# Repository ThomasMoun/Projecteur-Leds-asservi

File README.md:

# Projecteur-Leds-asservi  

<p align="center"> 

|Etudiants en charge du projet |       
|:----------------------------:|       
|Tom Charbonneau               |       
|Baptiste Gilles               |       
|Ludovic Sercy                 |
|Thomas Mouneyrat              |
|Bassem Barakat                |
|Quentin de La Chaise          |

|Professeurs encadrants le projet |
|:-------------------------------:|
|Nicolas Papazoglou               |
|Laurent Fiack                    |

*N.B. : Ce README s'adresse aux futurs ensearques qui auront le courage de s'aventurer sur le sinueux chemin de ce projet ; il s'adresse aussi aux électroniciens curieux et avide de découvertes ; enfin il s'adresse évidemment à nos chers professeurs.*

## Introduction

Le projecteur Leds est, comme son nom l'indique, un structure permettant l'éclairage coloré et la mise en valeur de décor dans différents évènements plus ou moins festifs.
Un projecteur de ce type doit pouvoir bouger suivant différents axes (2 dans notre cas Tilt-Pan) et le zoom ainsi que la couleur de la lumière émise doivent être ajustables.
Ce projet s'inscrit donc dans les domaines de la lumière et du son, et serait en théorie piloté par un régisseur lors d'évènements.
Ainsi, à la fin de la conception de ce projet on doit pouvoir être capable de le faire bouger en choisissant la direction et l'axe de mouvement, on doit aussi être en mesure de changer la couleur et de centrer la lumière sur des zones précises (tout cela via un unique contrôleur).

## Organisation du dépôt git

Dans ce dépôts git vous trouverez une branche pour chaque grand axe de travail du projet : 
 - Les différentes carte (Led, Alimentation, contrôle etc)
 - La partie mécanique (modélisation 3D)
 - Les parties drivers (moteurs, leds)
 
Dans la branche principale vous trouverez aussi les schémas utilisés dans ce README.

*Logiciels utilisés*

|Conception/Design PCB | Modélisation 3D | Programmation des cartes et définition des connexions |
|:--------------------:|:---------------:|:-----------------------------------------------------:|
|KiCAD 6.0             |Onshape          |STM32CubeIDE et STM32CubeMX                            |

|Alternatives possibles                                                                          |
|:----------------------------------------------------------------------------------------------:|
|Eagle (PCB)     /    Solidworks (onshape a l'avantage d'être gratuit)                           |

|Gestion de projet                                                                               |
|:----------------------------------------------------------------------------------------------:|
|Google Drive/Github/Redmine de l'école                                                          |                   

## Schémas d'architecture Hardware et/ou Software

_<p align = center>Schéma structurel associé à la structure 3D</p>_

*<p align =center>Schéma général d'architecture</p>*

*<p align = center>Schéma commande et puissance</p>*

Ce schéma nous a permis de synthétiser "qui a quel rôle" en commande et en alimentation

## Documentation

*Ce qui marche/Ce qui marche pas*

Général : 

-La carte d'alimentation semble fontionner bien qu'elle n'est pas été testé avec tout, elle possède tous les composants nécessaire à l'alimentation de l'ensemble
- Le réglage en intensité (via le contôleur) de la led issu du pcb "led test" fonctionne, le code qui passe par le DMX est donc correcte.
- Le mouvement du projecteur via le pilotage des moteurs n'est pas fiable, le code et des poids structurels sont à revoir.
- L'architecture du PCB de contrôle est correcte dans l'ensemble et possède tous les composants nécéssaires au bon fonctionnement du projecteur. Le régulateur linéaire est à déplacer car, suite à un soucis d'impression de via, on a rencontré des difficultés à le souder correctement empêchant son fonctionnement. Certaines capacités de découplage sont potentiellement à rapprocher du projecteur.

Point mécanique : 

Certaines des pièces sont à revoir pour la conception, il s'agit d'un prototype et il comporte beaucoup de défaut.

Défaut:
- Axe difficile à monter sur la pièce en U, il faut tordre la pièce en U pour insérer l'axe.
- Pas de buté axial sur l'axe
- tolérance des trous pas assez grands
- Solidité des axes des engrenages faibles
- Cage des engrenages trop rigide
- Montage des vis de la tête de projecteur impossible à cause de la structure en U qui empêche son accès
- Les vis de maintien entre la base et la partie tournante du projecteur étaient difficilement accessibles
    
## TODO
 
- Il reste une grosse partie programmation notamment pour le processeur de la carte de contrôle (centralisation des codes) et le pilotage des moteurs
- La carte Leds complète a été designé, il faut l'imprimer une première fois et la tester
- Reste à traiter le ventilateur ou un système de refroidissement de la struture (ventilo prévue dans la carte d'alimentation)
- Dans la lignée du ventilo, à voir pour un changement de matériau pour la structure ; l'ensemble est amené à chauffer
- Le zoom est une partie qu'on a très peu traité faute de temps, le projet de base est d'utiliser des lentilles placées devant chaque leds et qu'on viendrait éloignées ou rapprochées des leds pour zoomer. Le mouvement se ferait au travers d'un axe interne au projecteur (prévu dans la structure

Point mécanique :
 
Amélioration :
-Tolérance plus grande
-Utiliser un filetage dans les trous au lieu de vis + écrou
-Certains axes pas assez dimensionner pour résister aux contraintes
-Faire une structure moins rigide pour la cage des engrenages

## Deux points techniques importants    
        
### Le DMX

Afin de pouvoir contrôler le projecteur, nous utilisons une table DMX. Celle-ci est composée de différents curseurs, chacun pouvant contrôler un paramètre différent du projecteur. Les paramètres sont les suivants :
- le TILT
- le PAN
- le Zoom
- la couleur

Certains paramètres nécessitent plusieurs curseurs. En effet, un curseur permet de sélectionner une valeur entre 0 et 255. Pour les moteurs, par exemple, comme nous désirons pouvoir faire une rotation du projecteur de 540 degrés de tilt et 270 degrés de pan, et que les moteurs pas a pas choisi (NEMA 17) ont une résolution de 1,8 degré par pas et que nous désirons implémenter le microstepping pour plus de précision, il est nécessaire d’utiliser plusieurs curseurs. De la même manière, pour contrôler les LEDs, il faut choisir avec des curseurs indépendants les valeurs de Rouge, Vert, Bleu et Blanc.

La table DMX utilise le protocole DMX 512, cela permet d’utiliser un seul câble avec paire différentiel pour contrôler un grand nombre de paramètres et d’appareils. La trame DMX se présente de cette manière :

*<p align =center>Trame DMX</p>*

Chaque trame commence par un Break puis un MAB. Il y a ensuite 513 canaux DMX, le premier est le start code qui est utilisé pour paramétrer certains appareils mais inutile dans notre cas. Les 512 canaux suivants contiennent les valeurs prises par les différents curseurs.

Le signal étant transmis sur une paire différentielle, il est nécessaire pour le décoder de le passer sur un seul fil. Pour cela, on utilise un transmitter RS-485. 
Afin de décoder la trame DMX, on utilise de l’UART. Il est nécessaire de détecter le début de la trame pour pouvoir connaitre les valeurs correspondantes aux bons curseurs. Pour cela on utilise une Frame Error de l’UART.

Une fois ces valeurs récupérées, on peut les transmettre aux drivers moteurs et LEDs pour effectuer les actions demandées.

### Driver Moteur

#### Le fonctionnement

L’objectif était de réaliser des drivers pour des moteurs pas a pas capable de faire du microstepping. Chaque driver est composé d’un STM32G0 en communication avec le PCB de contrôle qui lui fourni la position à atteindre. Le STM32 pilote ensuite des ponts en H associés aux deux phases du moteur.

Les moteurs choisis sont des NEMA 14 et NEMA 17, chacun de ces moteurs possède des caractéristiques différentes mais comme ils seront asservi en courant, on peut conserver le même driver et le programmer différemment pour éviter que ceux-ci ne grillent. Ces moteurs sont composés de deux phases A et B, ce sont les enroulements des moteurs. Ces enroulements permettent de créer un champ magnétique permettant d’orienter le stator dans la direction voulu.

<p align =center><i>Phases du moteur</i></p>

Pour alimenter les enroulements, on utilise deux ponts en H ce qui nous permet de choisir le sens d’alimentation de chacune des phases.

<p align =center><i>Les deux états du pont en H</i></p>

En full step, ces phases sont alimentées alternativement dans un sens puis dans l’autre de manière à orienter le stator dans l’axe des enroulements.

<p align =center><i>Ordre d'alimentation des phases</i></p>

Pour le microstepping, on alimente simultanément les deux phases à différentes intensités afin d’aligner le rotor entre deux phases, cela nous permet d’augmenter le nombre de pas. On utilise le wave microstepping pour garder un couple constant au cours du temps.

<p align =center><i>Ordre d'alimentation des phases pour le Half-Step</i></p>

Pour un plus grand nombre de pas, on obtient les formes de courant suivantes :

On peut donc relier le courant au numéro du pas désiré par les équations suivantes :
- Ia = sin(num_pas * 360/32) * Imax
- Ib = cos(num_pas * 360/32) * Imax

Afin de d’asservir le courant arrivant dans chaque phase, on utilise un hacheur et un détecteur de courant pour chaque phase.

### Améliorations

- Le PCB n’ayant pas fonctionné, il est nécéssaire d’effectuer de nouveaux tests.
- Afin de pouvoir asservir le courant, il faut soit rajouter un hacheur soit dissocier les deux cotés de chaque pont en H pour pouvoir l'utiliser en hacheur (cette methode nécéssite des sorties PWM supplémentaires sur le STM32).
- Choisir mieux les composants pour qu'ils aient des tensions d'alimentation similaires afin de réduire le nombre de tensions d'alimentations différentes sur le driver.

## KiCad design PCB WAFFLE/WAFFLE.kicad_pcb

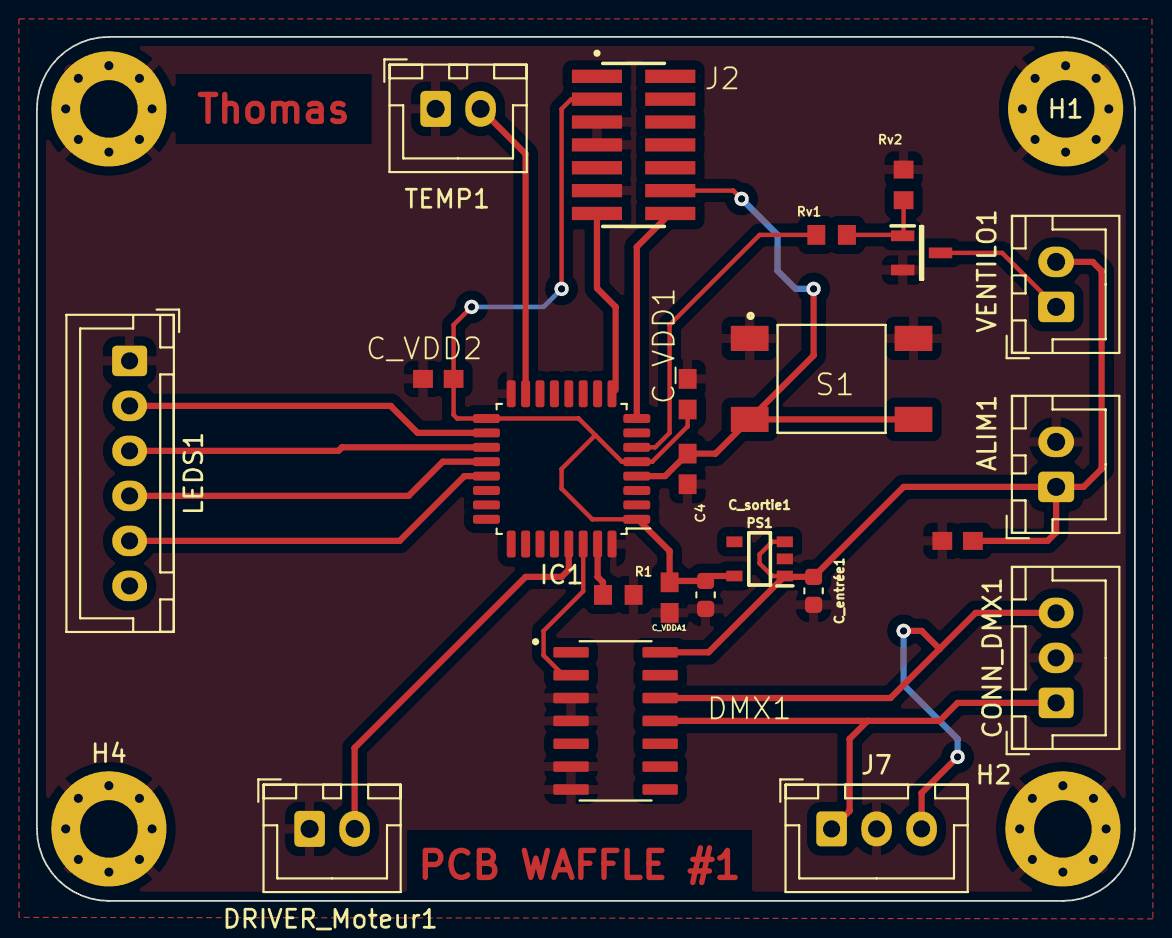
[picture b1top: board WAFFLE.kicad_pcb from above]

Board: 2 copper layers, 61.0 x 48.0 mm, 27 parts (0 on the bottom side), 19 nets.

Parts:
ALIM1: Conn_01x02; JST_XH_B2B-XH-A_1x02_P2.50mm_Vertical
C4: 0.1uF; C0603
CONN_DMX1: Conn_01x03_Male; JST_XH_B3B-XH-A_1x03_P2.50mm_Vertical
C_Decoupl_Connecteur1: 100uF; C0603
C_VDD1, C_VDD2: 100nF; C0603
C_VDDA1: 100nF; C0603
C_entrée1: 1uF; C_0603_1608Metric
C_sortie1: 4.7uF; C_0603_1608Metric
DMX1: SOIC127P600X175-14N
DRIVER_Moteur1: Conn_01x02; JST_XH_B2B-XH-A_1x02_P2.50mm_Vertical
H1, H2, H3, H4: MountingHole_Pad; MountingHole_3.2mm_M3_Pad_Via
IC1: STM32L412KBT6; LQFP-32_7x7mm_P0.8mm
J2: FTSH-107-01-L-DV; SAMTEC_FTSH-107-01-L-DV
J7: Conn_01x03_Male; JST_XH_B3B-XH-A_1x03_P2.50mm_Vertical
LEDS1: PINHD-1X6; JST_XH_B6B-XH-A_1x06_P2.50mm_Vertical
PS1: BU33SD5WG-TR; RegLIN
Q1: SQ2310ES-T1_GE3; SOT95P237X112-3N
R1: 100k; R0603
Rv1: 22; R0603
Rv2: 10k; R0603
S1: 2-1437565-7; SW_2-1437565-7
TEMP1: Conn_01x02; JST_XH_B2B-XH-A_1x02_P2.50mm_Vertical
VENTILO1: Conn_01x02; JST_XH_B2B-XH-A_1x02_P2.50mm_Vertical

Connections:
+3.3V: C_VDD1.1, C_VDD2.1, C_VDDA1.1, C_sortie1.1, IC1.1 (VDD_1), IC1.5 (VDDA/VREF+), IC1.17 (VDD_2), J2.03, PS1.5 (VOUT)
+5V: ALIM1.1, C_Decoupl_Connecteur1.2, C_entrée1.1, DMX1.14 (VCC), PS1.1 (VIN), PS1.3 (STBY), VENTILO1.2
ADC_Température_ventilo: IC1.15 (PB1), TEMP1.2
GND: ALIM1.2, C4.2, CONN_DMX1.2, C_Decoupl_Connecteur1.1, C_VDD1.2, C_VDD2.2, C_VDDA1.2, C_entrée1.2, C_sortie1.2, DMX1.3 (RE/), DMX1.4 (DE), DMX1.6 (GND_1), DMX1.7 (GND_2), DRIVER_Moteur1.1, H1.1, H2.1, H3.1, H4.1, IC1.16 (VSS_1), IC1.32 (VSS_2), J2.05, J2.07, J2.11, J7.2, LEDS1.1, PS1.2 (GND), Q1.2, R1.2, Rv2.1, S1.1, S1.2, TEMP1.1
NRST: C4.1, IC1.4 (NRST), J2.12, S1.3, S1.4
unnamed: CONN_DMX1.1, DMX1.11 (B), J7.1
unnamed: CONN_DMX1.3, DMX1.12 (A), J7.3
unnamed: IC1.31 (PH3-BOOT0), R1.1
unnamed: Q1.1, Rv1.2, Rv2.2
unnamed: Q1.3, VENTILO1.1
PWM_Leds_B: IC1.19 (PA9), LEDS1.3
PWM_Leds_G: IC1.20 (PA10), LEDS1.4
PWM_Leds_R: IC1.21 (PA11), LEDS1.5
PWM_Leds_W: IC1.18 (PA8), LEDS1.2
PWM_Ventilateur: IC1.6 (PA0-CK_IN), Rv1.1
UART_Driver_moteur: DRIVER_Moteur1.2, IC1.29 (PB6)
UART_RS485_DMX: DMX1.2 (RO), IC1.30 (PB7)
VCP_UART_RX: IC1.9 (PA3), J2.13
VCP_UART_TX: IC1.8 (PA2), J2.14

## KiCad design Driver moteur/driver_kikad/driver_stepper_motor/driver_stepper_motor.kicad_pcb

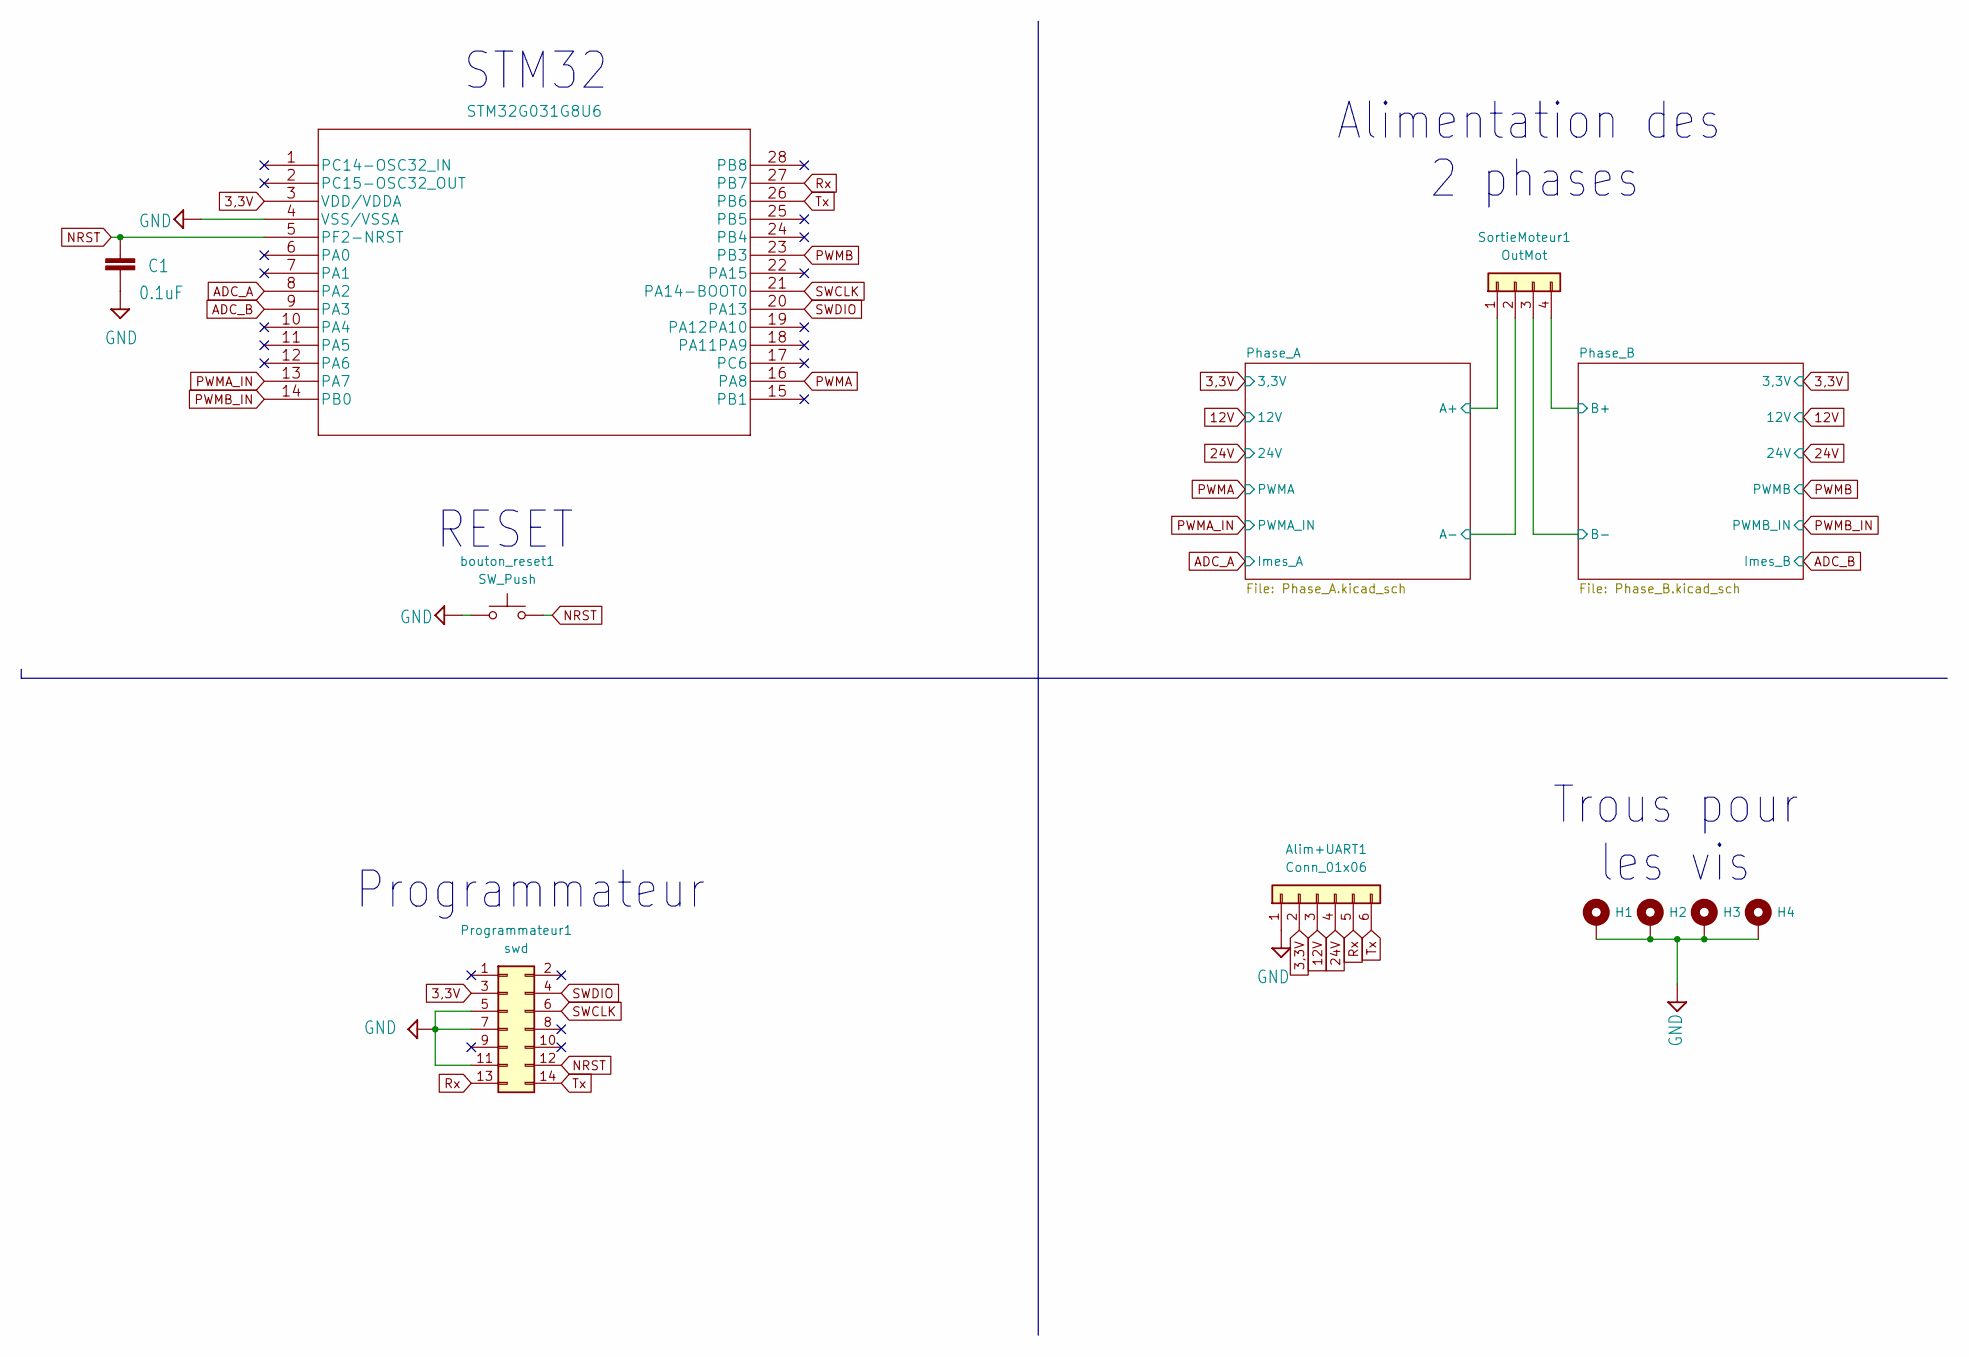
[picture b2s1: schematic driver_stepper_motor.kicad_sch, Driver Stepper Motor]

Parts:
Alim+UART1: Conn_01x06; JST_XH_B6B-XH-A_1x06_P2.50mm_Vertical
C1: 0.1uF; C_0603_1608Metric
H1, H2, H3, H4: MountingHole_Pad; MountingHole_3.2mm_M3_Pad_Via
Programmateur1: swd; PinHeader_2x07_P1.27mm_Vertical_SMD
SortieMoteur1: OutMot; JST_XH_B4B-XH-A_1x04_P2.50mm_Vertical
U1: STM32G031G8U6; QFN-28_4x4mm_P0.5mm
bouton_reset1: SW_Push; SW_2-1437565-7

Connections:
3,3V: Alim+UART1.2, Programmateur1.3, U1.3 (VDD/VDDA); also elsewhere on the board
12V: Alim+UART1.3; also elsewhere on the board
24V: Alim+UART1.4; also elsewhere on the board
/Phase_A/A+: SortieMoteur1.1; also elsewhere on the board
/Phase_A/A-: SortieMoteur1.2; also elsewhere on the board
/Phase_B/B+: SortieMoteur1.4; also elsewhere on the board
/Phase_B/B-: SortieMoteur1.3; also elsewhere on the board
ADC_A: U1.8 (PA2); also elsewhere on the board
ADC_B: U1.9 (PA3); also elsewhere on the board
GND: Alim+UART1.1, C1.2, H1.1, H2.1, H3.1, H4.1, Programmateur1.5, Programmateur1.7, Programmateur1.11, U1.4 (VSS/VSSA), bouton_reset1.1; also elsewhere on the board
NRST: C1.1, Programmateur1.12, U1.5 (PF2-NRST), bouton_reset1.2
PWMA: U1.16 (PA8); also elsewhere on the board
PWMA_IN: U1.13 (PA7); also elsewhere on the board
PWMB: U1.23 (PB3); also elsewhere on the board
PWMB_IN: U1.14 (PB0); also elsewhere on the board
Rx: Alim+UART1.5, Programmateur1.13, U1.27 (PB7)
SWCLK: Programmateur1.6, U1.21 (PA14-BOOT0)
SWDIO: Programmateur1.4, U1.20 (PA13)
Tx: Alim+UART1.6, Programmateur1.14, U1.26 (PB6)

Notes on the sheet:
Trous pour les vis
RESET
Programmateur
STM32
Alimentation des 2 phases

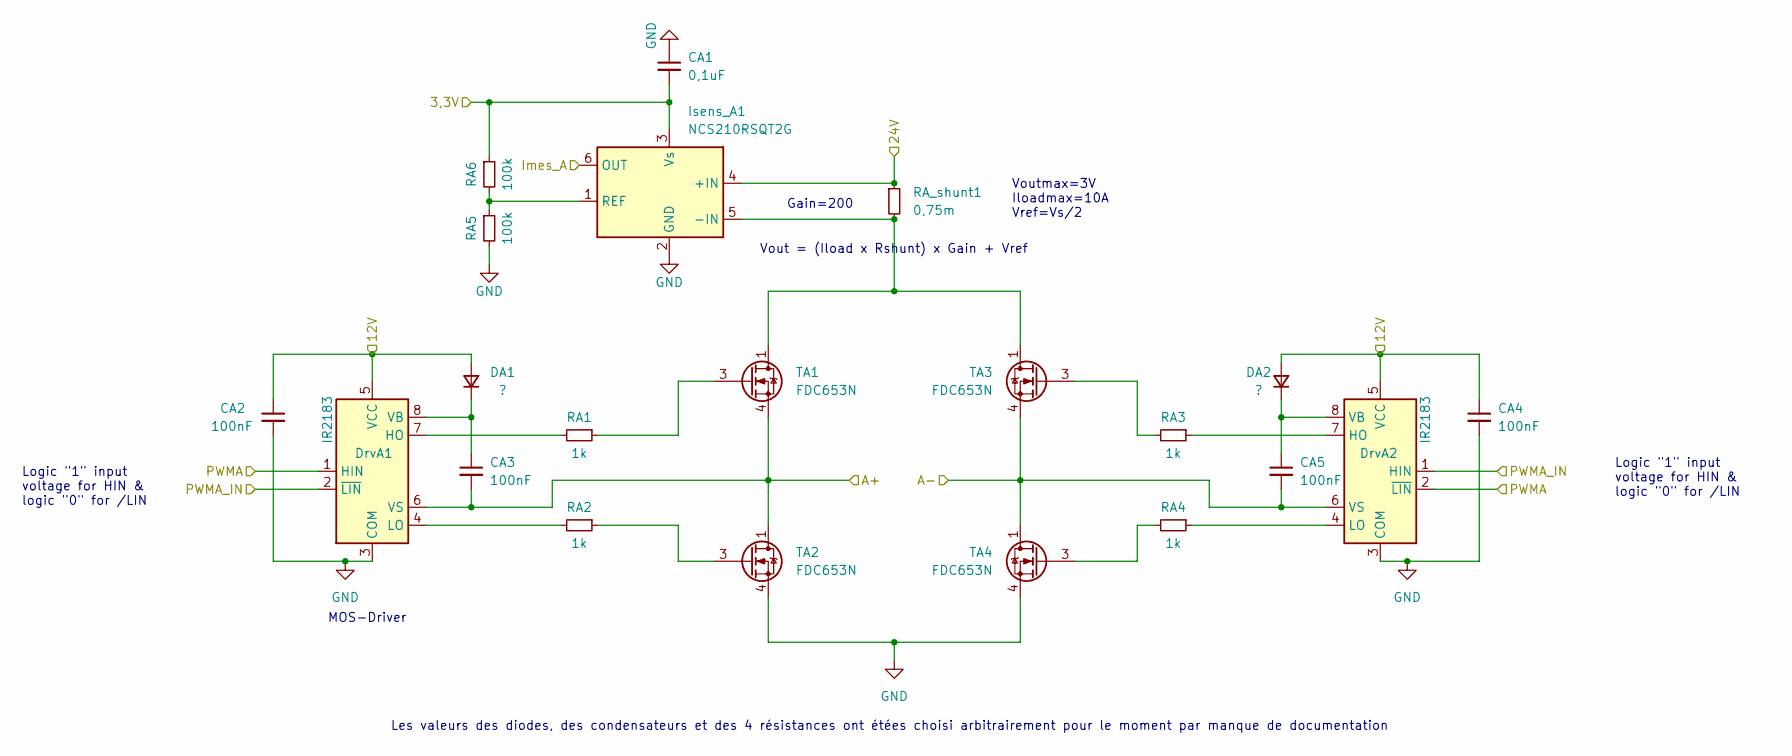
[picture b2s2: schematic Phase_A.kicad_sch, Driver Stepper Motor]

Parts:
CA1: 0,1uF; C_0603_1608Metric
CA2, CA3, CA4, CA5: 100nF; C_0603_1608Metric
DA1, DA2: ?; D_0603_1608Metric
DrvA1, DrvA2: IR2183; SOIC-8_3.9x4.9mm_P1.27mm
Isens_A1: NCS210RSQT2G; SOT-363_SC-70-6
RA1, RA2, RA3, RA4: 1k; R_0603_1608Metric
RA5, RA6: 100k; R_0603_1608Metric
RA_shunt1: 0,75m; R_0603_1608Metric
TA1, TA2, TA3, TA4: FDC653N; SuperSOT-6

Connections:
3,3V: CA1.2, Isens_A1.3 (Vs), RA6.1; also elsewhere on the board
12V: CA2.1, CA4.1, DA1.2 (A), DA2.2 (A), DrvA1.5 (VCC), DrvA2.5 (VCC); also elsewhere on the board
24V: Isens_A1.4 (+IN), RA_shunt1.1; also elsewhere on the board
/Phase_A/A+: CA3.2, DrvA1.6 (VS), TA1.4 (S), TA2.1 (D), TA2.2 (D), TA2.5 (D), TA2.6 (D); also elsewhere on the board
/Phase_A/A-: CA5.2, DrvA2.6 (VS), TA3.4 (S), TA4.1 (D), TA4.2 (D), TA4.5 (D), TA4.6 (D); also elsewhere on the board
ADC_A: Isens_A1.6 (OUT); also elsewhere on the board
GND: CA1.1, CA2.2, CA4.2, DrvA1.3 (COM), DrvA2.3 (COM), Isens_A1.2 (GND), RA5.2, TA2.4 (S), TA4.4 (S); also elsewhere on the board
unnamed: CA3.1, DA1.1 (K), DrvA1.8 (VB)
unnamed: CA5.1, DA2.1 (K), DrvA2.8 (VB)
unnamed: DrvA1.4 (LO), RA2.2
unnamed: DrvA1.7 (HO), RA1.2
unnamed: DrvA2.4 (LO), RA4.1
unnamed: DrvA2.7 (HO), RA3.1
unnamed: Isens_A1.1 (REF), RA5.1, RA6.2
unnamed: Isens_A1.5 (-IN), RA_shunt1.2, TA1.1 (D), TA1.2 (D), TA1.5 (D), TA1.6 (D), TA3.1 (D), TA3.2 (D), TA3.5 (D), TA3.6 (D)
unnamed: RA1.1, TA1.3 (G)
unnamed: RA2.1, TA2.3 (G)
unnamed: RA3.2, TA3.3 (G)
unnamed: RA4.2, TA4.3 (G)
PWMA: DrvA1.1 (HIN), DrvA2.2 (~LIN); also elsewhere on the board
PWMA_IN: DrvA1.2 (~LIN), DrvA2.1 (HIN); also elsewhere on the board

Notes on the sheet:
MOS-Driver
Gain=200
Logic "1" input voltage for HIN & logic "0" for /LIN
Vout = (Iload x Rshunt) x Gain + Vref
Voutmax=3V Iloadmax=10A Vref=Vs/2
Les valeurs des diodes, des condensateurs et des 4 résistances ont étées choisi arbitrairement pour le moment par manque de documentation

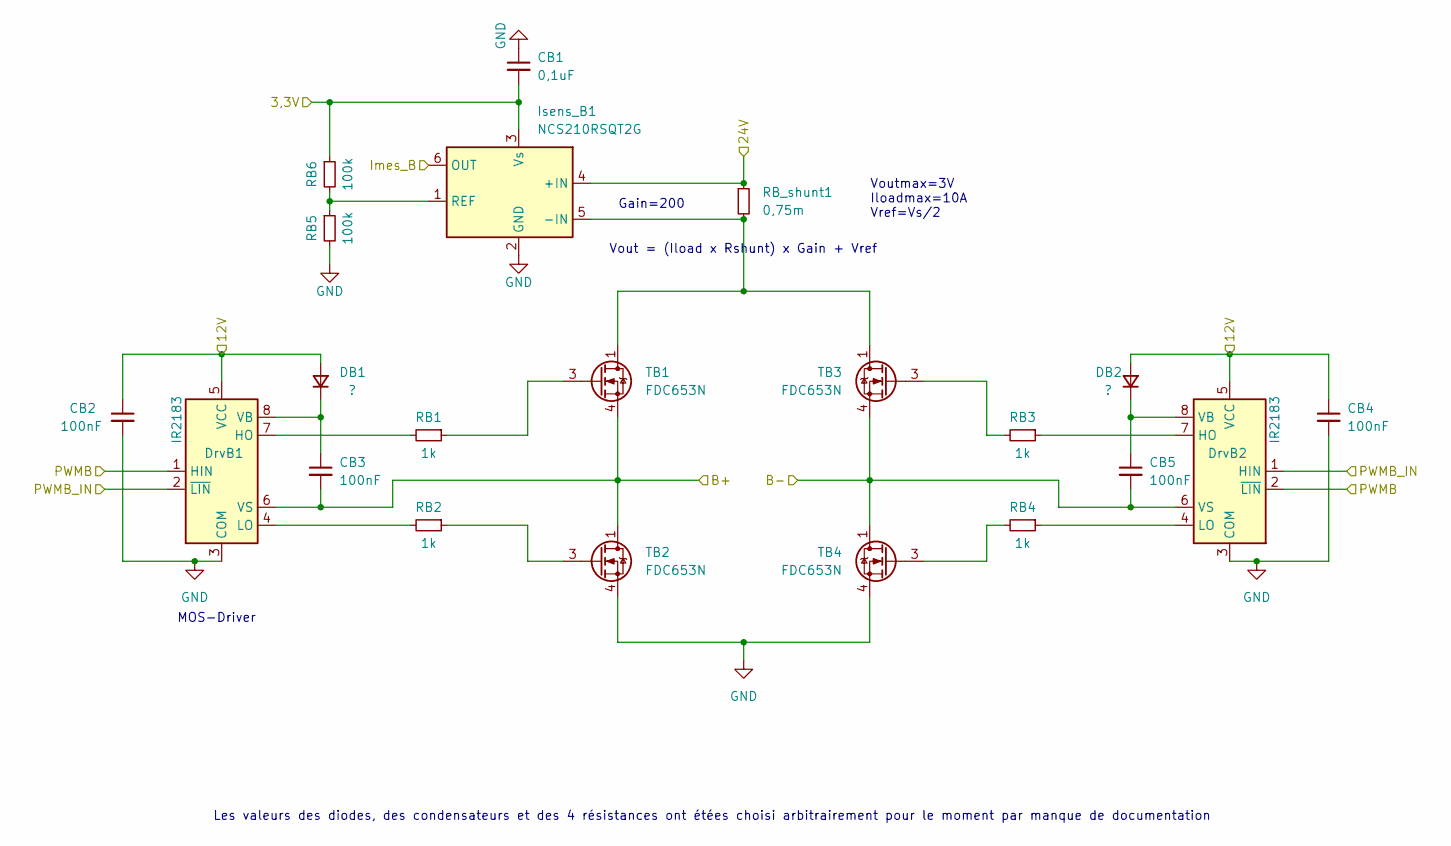
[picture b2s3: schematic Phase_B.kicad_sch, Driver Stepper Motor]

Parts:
CB1: 0,1uF; C_0603_1608Metric
CB2, CB3, CB4, CB5: 100nF; C_0603_1608Metric
DB1, DB2: ?; D_0603_1608Metric
DrvB1, DrvB2: IR2183; SOIC-8_3.9x4.9mm_P1.27mm
Isens_B1: NCS210RSQT2G; SOT-363_SC-70-6
RB1, RB2, RB3, RB4: 1k; R_0603_1608Metric
RB5, RB6: 100k; R_0603_1608Metric
RB_shunt1: 0,75m; R_0603_1608Metric
TB1, TB2, TB3, TB4: FDC653N; SuperSOT-6

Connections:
3,3V: CB1.2, Isens_B1.3 (Vs), RB6.1; also elsewhere on the board
12V: CB2.1, CB4.1, DB1.2 (A), DB2.2 (A), DrvB1.5 (VCC), DrvB2.5 (VCC); also elsewhere on the board
24V: Isens_B1.4 (+IN), RB_shunt1.1; also elsewhere on the board
/Phase_B/B+: CB3.2, DrvB1.6 (VS), TB1.4 (S), TB2.1 (D), TB2.2 (D), TB2.5 (D), TB2.6 (D); also elsewhere on the board
/Phase_B/B-: CB5.2, DrvB2.6 (VS), TB3.4 (S), TB4.1 (D), TB4.2 (D), TB4.5 (D), TB4.6 (D); also elsewhere on the board
ADC_B: Isens_B1.6 (OUT); also elsewhere on the board
GND: CB1.1, CB2.2, CB4.2, DrvB1.3 (COM), DrvB2.3 (COM), Isens_B1.2 (GND), RB5.2, TB2.4 (S), TB4.4 (S); also elsewhere on the board
unnamed: CB3.1, DB1.1 (K), DrvB1.8 (VB)
unnamed: CB5.1, DB2.1 (K), DrvB2.8 (VB)
unnamed: DrvB1.4 (LO), RB2.2
unnamed: DrvB1.7 (HO), RB1.2
unnamed: DrvB2.4 (LO), RB4.1
unnamed: DrvB2.7 (HO), RB3.1
unnamed: Isens_B1.1 (REF), RB5.1, RB6.2
unnamed: Isens_B1.5 (-IN), RB_shunt1.2, TB1.1 (D), TB1.2 (D), TB1.5 (D), TB1.6 (D), TB3.1 (D), TB3.2 (D), TB3.5 (D), TB3.6 (D)
unnamed: RB1.1, TB1.3 (G)
unnamed: RB2.1, TB2.3 (G)
unnamed: RB3.2, TB3.3 (G)
unnamed: RB4.2, TB4.3 (G)
PWMB: DrvB1.1 (HIN), DrvB2.2 (~LIN); also elsewhere on the board
PWMB_IN: DrvB1.2 (~LIN), DrvB2.1 (HIN); also elsewhere on the board

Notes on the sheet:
Gain=200
MOS-Driver
Vout = (Iload x Rshunt) x Gain + Vref
Voutmax=3V Iloadmax=10A Vref=Vs/2
Les valeurs des diodes, des condensateurs et des 4 résistances ont étées choisi arbitrairement pour le moment par manque de documentation

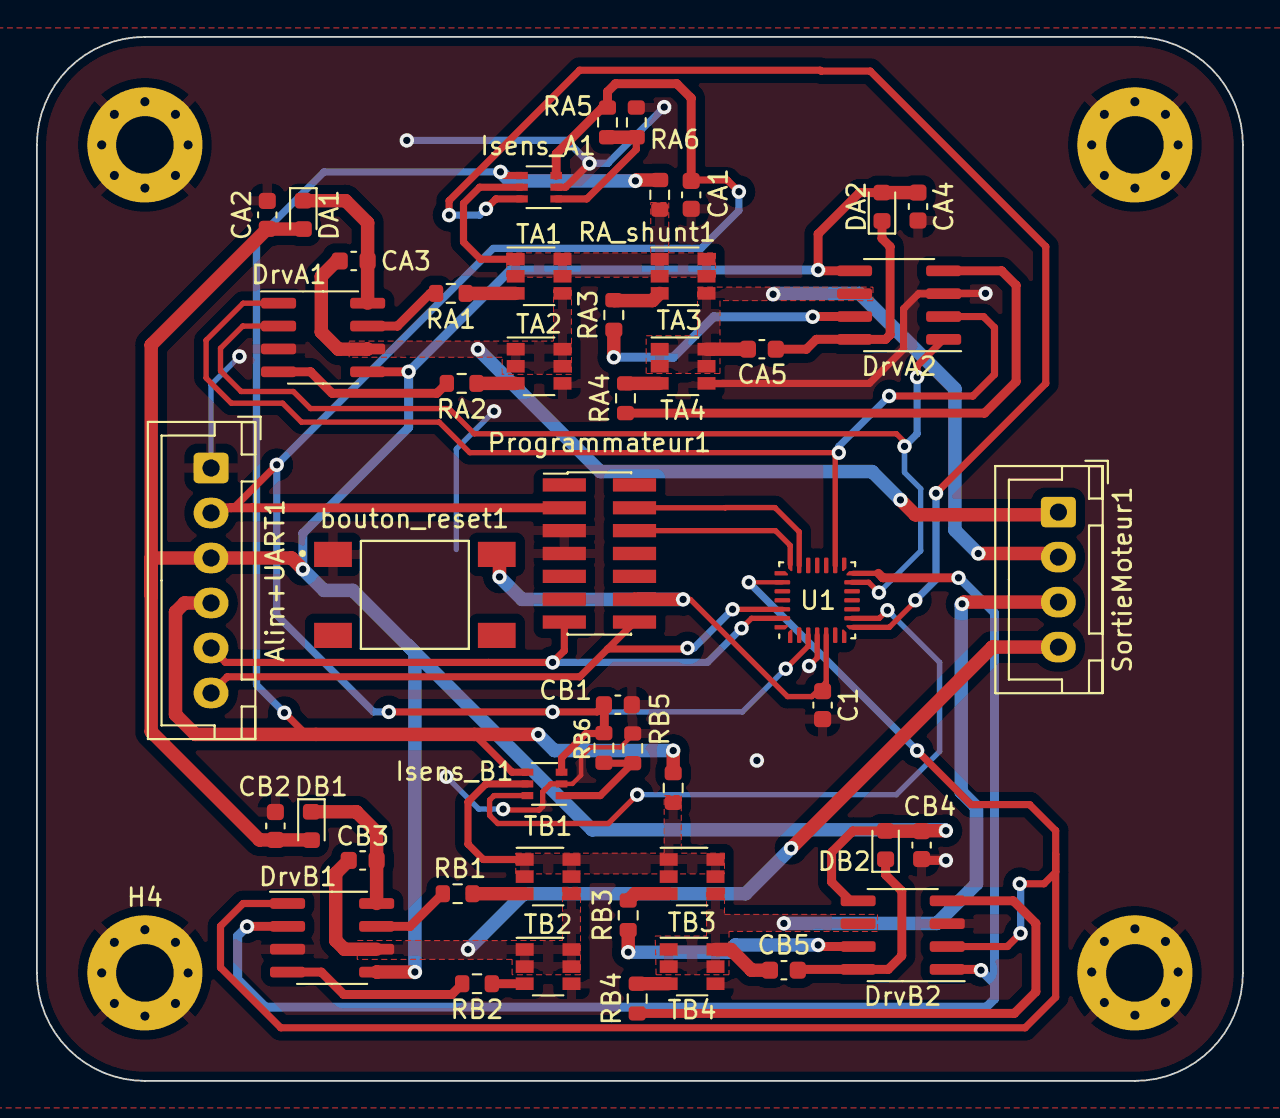
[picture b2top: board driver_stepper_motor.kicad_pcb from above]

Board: 2 copper layers, 67.0 x 58.0 mm, 52 parts (0 on the bottom side), 43 nets.

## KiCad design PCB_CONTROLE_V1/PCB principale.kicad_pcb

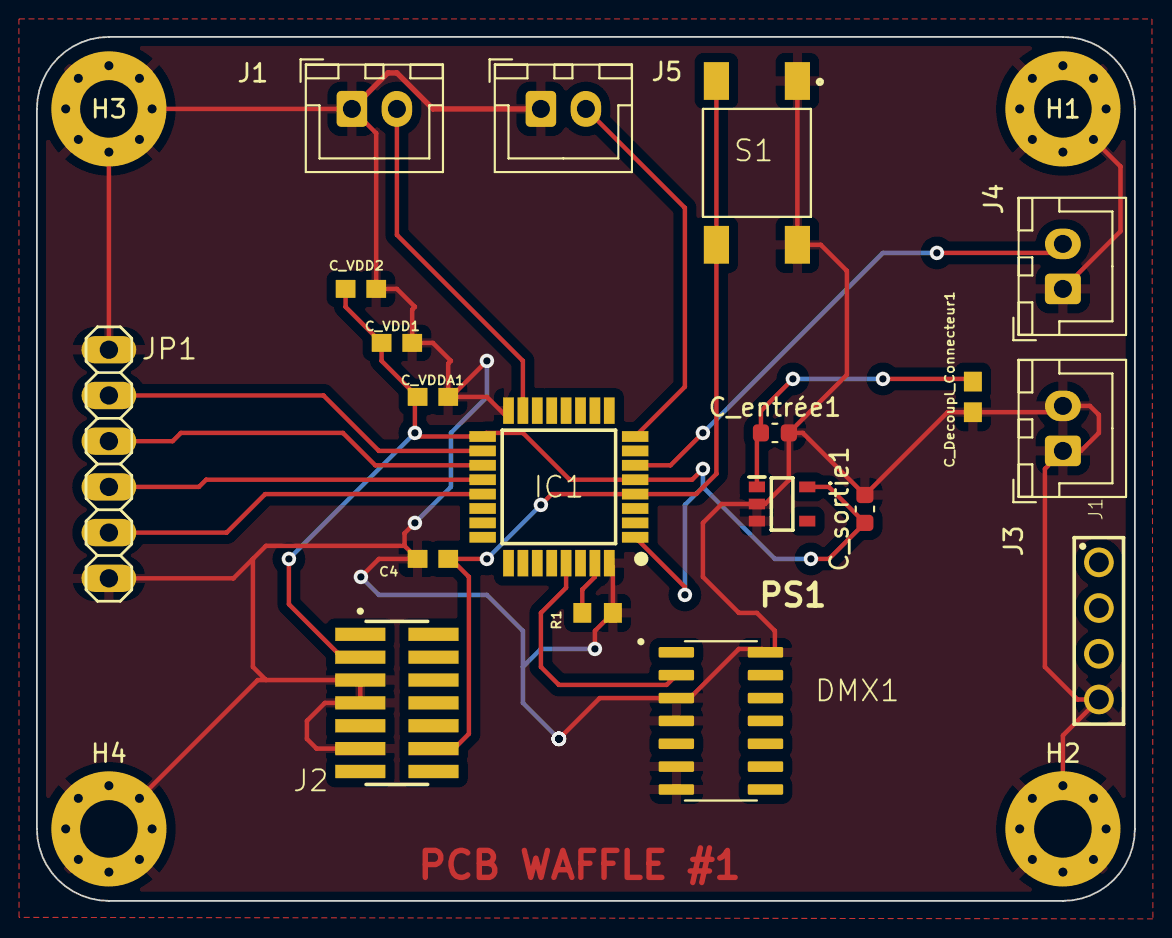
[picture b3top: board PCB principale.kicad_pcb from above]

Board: 2 copper layers, 61.0 x 48.0 mm, 23 parts (0 on the bottom side), 13 nets.

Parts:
C4: 0.1uF; C0603
C_Decoupl_Connecteur1: 100uF; C0603
C_VDD1, C_VDD2: 100nF; C0603
C_VDDA1: 100nF; C0603
C_entrée1: 1uF; C_0603_1608Metric
C_sortie1: 1uF; C_0603_1608Metric
DMX1: SOIC127P600X175-14N
H1, H2, H3, H4: MountingHole_Pad; MountingHole_3.2mm_M3_Pad_Via
IC1: STM32L412KBT6; QFP80P900X900X160-32N
J1, J3, J4, J5: Conn_01x02; JST_XH_B2B-XH-A_1x02_P2.50mm_Vertical
J1#2: 61300411121
J2: FTSH-107-01-L-DV; SAMTEC_FTSH-107-01-L-DV
JP1: PINHD-1X6; 1X06
PS1: BU33SD5WG-TR; SOT95P280X125-5N
R1: 100k; R0603
S1: 2-1437565-7; SW_2-1437565-7

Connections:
5V_RegLin_RSDMX: C4.2, C_Decoupl_Connecteur1.1, C_VDD1.2, C_VDD2.2, C_VDDA1.2, C_entrée1.2, C_sortie1.2, DMX1.3 (RE/), DMX1.4 (DE), DMX1.6 (GND_1), DMX1.7 (GND_2), DMX1.14 (VCC), H1.1, H2.1, H3.1, H4.1, IC1.16 (VSS_1), IC1.32 (VSS_2), J1.1, J1#2.4, J2.05, J2.07, J2.11, J3.1, J3.2, J4.1, J5.1, JP1.1, JP1.6, PS1.2 (GND), PS1.3 (STBY), R1.2, S1.1, S1.2
+3.3V: C_VDD1.1, C_VDD2.1, C_VDDA1.1, C_sortie1.1, IC1.1 (VDD_1), IC1.5 (VDDA/VREF+), IC1.17 (VDD_2), J2.03, PS1.5 (VOUT)
ADC_Température_ventilo: IC1.15 (PB1), J1.2
NRST: C4.1, IC1.4 (NRST), J2.12, S1.3, S1.4
unnamed: C_Decoupl_Connecteur1.2, C_entrée1.1, PS1.1 (VIN)
unnamed: IC1.31 (PH3-BOOT0), R1.1
PWM_Leds_B: IC1.19 (PA9), JP1.3
PWM_Leds_G: IC1.20 (PA10), JP1.4
PWM_Leds_R: IC1.21 (PA11), JP1.5
PWM_Leds_W: IC1.18 (PA8), JP1.2
PWM_Ventilateur: IC1.6 (PA0-CK_IN), J4.2
UART_Driver_moteur: IC1.8 (PA2), J5.2
UART_RS485_DMX: DMX1.2 (RO), IC1.29 (PB6)

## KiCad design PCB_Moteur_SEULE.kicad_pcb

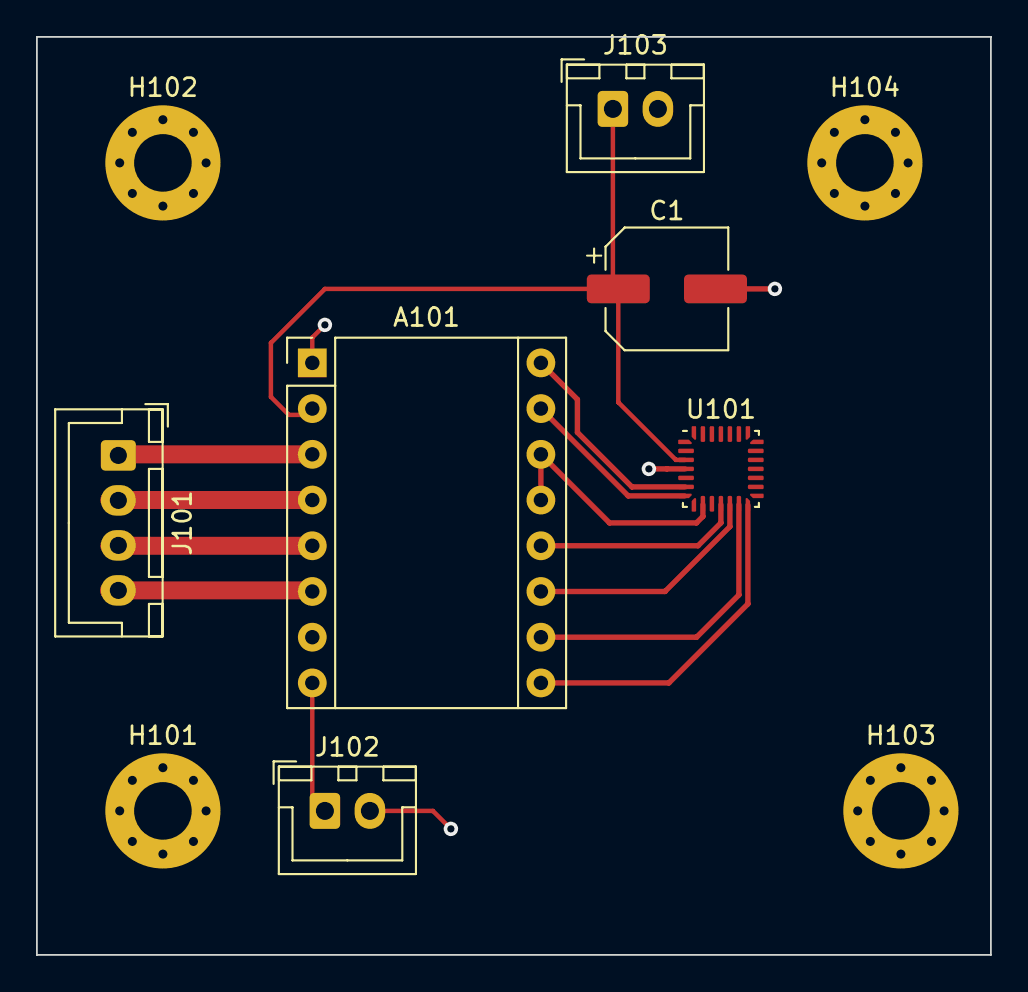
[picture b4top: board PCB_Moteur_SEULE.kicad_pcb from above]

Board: 2 copper layers, 53.0 x 51.0 mm, 10 parts (0 on the bottom side), 14 nets.

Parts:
A101: Pololu_Breakout_A4988; Pololu_Breakout-16_15.2x20.3mm
C1: 100µF; CP_Elec_6.3x7.7
H101, H102, H103, H104: MountingHole_Pad; MountingHole_3.2mm_M3_Pad_Via
J101: Conn_01x04 (Phases MOTEUR); JST_XH_B4B-XH-A_1x04_P2.50mm_Vertical
J102: Conn_01x02(ALIM MOTEUR); JST_XH_B2B-XH-A_1x02_P2.50mm_Vertical
J103: Conn_01x02 (ALIM processeur); JST_XH_B2B-XH-A_1x02_P2.50mm_Vertical
U101: STM32G031G8U6; QFN-28_4x4mm_P0.5mm

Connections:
/1A: A101.4 (1A), J101.2
/1B: A101.3 (1B), J101.1
/2A: A101.5 (2A), J101.3
/2B: A101.6 (2B), J101.4
/VMOT_12V: A101.8 (VMOT), J102.1
DIR: A101.16 (DIR), U101.6 (PA0)
ENABLE: A101.9 (~ENABLE), U101.14 (PB0)
GND: A101.1 (GND), A101.7 (GND), C1.2, H101.1, H102.1, H103.1, H104.1, J102.2, J103.2, U101.4 (VSS/VSSA)
MS1: A101.10 (MS1), U101.13 (PA7)
MS2: A101.11 (MS2), U101.12 (PA6)
MS3: A101.12 (MS3), U101.11 (PA5)
SLEEP: A101.13 (~RESET), A101.14 (~SLEEP), U101.9 (PA3)
STEP: A101.15 (STEP), U101.7 (PA1)
VCC_5V: A101.2 (VDD), C1.1, J103.1, U101.3 (VDD/VDDA)

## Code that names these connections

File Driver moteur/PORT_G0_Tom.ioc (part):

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Mcu.Name=STM32G031G(4-6-8)Ux
Mcu.Package=UFQFPN28
Mcu.UserName=STM32G031G8Ux
PA13.Mode=Serial_Wire
PA13.Signal=SYS_SWDIO
PA14-BOOT0.Mode=Serial_Wire
PA14-BOOT0.Signal=SYS_SWCLK
PA2.Mode=IN2
PA2.Signal=ADC1_IN2
PA3.Mode=IN3
PA3.Signal=ADC1_IN3
PA7.Mode=PWM Generation1 CH1 CH1N
PA7.Signal=TIM1_CH1N
PA8.Signal=S_TIM1_CH1
PB0.Mode=PWM Generation2 CH2 CH2N
PB0.Signal=TIM1_CH2N
PB3.Signal=S_TIM1_CH2
PB6.Mode=Asynchronous
PB6.Signal=USART1_TX
PB7.Mode=Asynchronous
PB7.Signal=USART1_RX
RCC.HSE_VALUE=8000000
RCC.SYSCLKFreq_VALUE=16000000
board=custom

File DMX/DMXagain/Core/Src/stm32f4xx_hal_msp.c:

/* USER CODE BEGIN Header */
/**
  ******************************************************************************
  * @file         stm32f4xx_hal_msp.c
  * @brief        This file provides code for the MSP Initialization
  *               and de-Initialization codes.
  ******************************************************************************
  * @attention
  *
  * Copyright (c) 2023 STMicroelectronics.
  * All rights reserved.
  *
  * This software is licensed under terms that can be found in the LICENSE file
  * in the root directory of this software component.
  * If no LICENSE file comes with this software, it is provided AS-IS.
  *
  ******************************************************************************
  */
/* USER CODE END Header */

/* Includes ------------------------------------------------------------------*/
#include "main.h"
/* USER CODE BEGIN Includes */

/* USER CODE END Includes */

/* Private typedef -----------------------------------------------------------*/
/* USER CODE BEGIN TD */

/* USER CODE END TD */

/* Private define ------------------------------------------------------------*/
/* USER CODE BEGIN Define */

/* USER CODE END Define */

/* Private macro -------------------------------------------------------------*/
/* USER CODE BEGIN Macro */

/* USER CODE END Macro */

/* Private variables ---------------------------------------------------------*/
/* USER CODE BEGIN PV */

/* USER CODE END PV */

/* Private function prototypes -----------------------------------------------*/
/* USER CODE BEGIN PFP */

/* USER CODE END PFP */

/* External functions --------------------------------------------------------*/
/* USER CODE BEGIN ExternalFunctions */

/* USER CODE END ExternalFunctions */

/* USER CODE BEGIN 0 */

/* USER CODE END 0 */

void HAL_TIM_MspPostInit(TIM_HandleTypeDef *htim);
                    /**
  * Initializes the Global MSP.
  */
void HAL_MspInit(void)
{
  /* USER CODE BEGIN MspInit 0 */

  /* USER CODE END MspInit 0 */

  __HAL_RCC_SYSCFG_CLK_ENABLE();
  __HAL_RCC_PWR_CLK_ENABLE();

  HAL_NVIC_SetPriorityGrouping(NVIC_PRIORITYGROUP_0);

  /* System interrupt init*/

  /* USER CODE BEGIN MspInit 1 */

  /* USER CODE END MspInit 1 */
}

/**
* @brief TIM_PWM MSP Initialization
* This function configures the hardware resources used in this example
* @param htim_pwm: TIM_PWM handle pointer
* @retval None
*/
void HAL_TIM_PWM_MspInit(TIM_HandleTypeDef* htim_pwm)
{
  if(htim_pwm->Instance==TIM1)
  {
  /* USER CODE BEGIN TIM1_MspInit 0 */

  /* USER CODE END TIM1_MspInit 0 */
    /* Peripheral clock enable */
    __HAL_RCC_TIM1_CLK_ENABLE();
  /* USER CODE BEGIN TIM1_MspInit 1 */

  /* USER CODE END TIM1_MspInit 1 */
  }

}

void HAL_TIM_MspPostInit(TIM_HandleTypeDef* htim)
{
  GPIO_InitTypeDef GPIO_InitStruct = {0};
  if(htim->Instance==TIM1)
  {
  /* USER CODE BEGIN TIM1_MspPostInit 0 */

  /* USER CODE END TIM1_MspPostInit 0 */

    __HAL_RCC_GPIOA_CLK_ENABLE();
    /**TIM1 GPIO Configuration
    PA7     ------> TIM1_CH1N
    PA8     ------> TIM1_CH1
    */
    GPIO_InitStruct.Pin = GPIO_PIN_7|GPIO_PIN_8;
    GPIO_InitStruct.Mode = GPIO_MODE_AF_PP;
    GPIO_InitStruct.Pull = GPIO_NOPULL;
    GPIO_InitStruct.Speed = GPIO_SPEED_FREQ_LOW;
    GPIO_InitStruct.Alternate = GPIO_AF1_TIM1;
    HAL_GPIO_Init(GPIOA, &GPIO_InitStruct);

  /* USER CODE BEGIN TIM1_MspPostInit 1 */

  /* USER CODE END TIM1_MspPostInit 1 */
  }

}
/**
* @brief TIM_PWM MSP De-Initialization
* This function freeze the hardware resources used in this example
* @param htim_pwm: TIM_PWM handle pointer
* @retval None
*/
void HAL_TIM_PWM_MspDeInit(TIM_HandleTypeDef* htim_pwm)
{
  if(htim_pwm->Instance==TIM1)
  {
  /* USER CODE BEGIN TIM1_MspDeInit 0 */

  /* USER CODE END TIM1_MspDeInit 0 */
    /* Peripheral clock disable */
    __HAL_RCC_TIM1_CLK_DISABLE();
  /* USER CODE BEGIN TIM1_MspDeInit 1 */

  /* USER CODE END TIM1_MspDeInit 1 */
  }

}

/**
* @brief UART MSP Initialization
* This function configures the hardware resources used in this example
* @param huart: UART handle pointer
* @retval None
*/
void HAL_UART_MspInit(UART_HandleTypeDef* huart)
{
  GPIO_InitTypeDef GPIO_InitStruct = {0};
  if(huart->Instance==USART1)
  {
  /* USER CODE BEGIN USART1_MspInit 0 */

  /* USER CODE END USART1_MspInit 0 */
    /* Peripheral clock enable */
    __HAL_RCC_USART1_CLK_ENABLE();

    __HAL_RCC_GPIOA_CLK_ENABLE();
    /**USART1 GPIO Configuration
    PA9     ------> USART1_TX
    PA10     ------> USART1_RX
    */
    GPIO_InitStruct.Pin = GPIO_PIN_9|GPIO_PIN_10;
    GPIO_InitStruct.Mode = GPIO_MODE_AF_PP;
    GPIO_InitStruct.Pull = GPIO_NOPULL;
    GPIO_InitStruct.Speed = GPIO_SPEED_FREQ_VERY_HIGH;
    GPIO_InitStruct.Alternate = GPIO_AF7_USART1;
    HAL_GPIO_Init(GPIOA, &GPIO_InitStruct);

    /* USART1 interrupt Init */
    HAL_NVIC_SetPriority(USART1_IRQn, 0, 0);
    HAL_NVIC_EnableIRQ(USART1_IRQn);
  /* USER CODE BEGIN USART1_MspInit 1 */

  /* USER CODE END USART1_MspInit 1 */
  }
  else if(huart->Instance==USART2)
  {
  /* USER CODE BEGIN USART2_MspInit 0 */

  /* USER CODE END USART2_MspInit 0 */
    /* Peripheral clock enable */
    __HAL_RCC_USART2_CLK_ENABLE();

    __HAL_RCC_GPIOA_CLK_ENABLE();
    /**USART2 GPIO Configuration
    PA2     ------> USART2_TX
    PA3     ------> USART2_RX
    */
    GPIO_InitStruct.Pin = USART_TX_Pin|USART_RX_Pin;
    GPIO_InitStruct.Mode = GPIO_MODE_AF_PP;
    GPIO_InitStruct.Pull = GPIO_NOPULL;
    GPIO_InitStruct.Speed = GPIO_SPEED_FREQ_VERY_HIGH;
    GPIO_InitStruct.Alternate = GPIO_AF7_USART2;
    HAL_GPIO_Init(GPIOA, &GPIO_InitStruct);

    /* USART2 interrupt Init */
    HAL_NVIC_SetPriority(USART2_IRQn, 0, 0);
    HAL_NVIC_EnableIRQ(USART2_IRQn);
  /* USER CODE BEGIN USART2_MspInit 1 */

  /* USER CODE END USART2_MspInit 1 */
  }

}

/**
* @brief UART MSP De-Initialization
* This function freeze the hardware resources used in this example
* @param huart: UART handle pointer
* @retval None
*/
void HAL_UART_MspDeInit(UART_HandleTypeDef* huart)
{
  if(huart->Instance==USART1)
  {
  /* USER CODE BEGIN USART1_MspDeInit 0 */

  /* USER CODE END USART1_MspDeInit 0 */
    /* Peripheral clock disable */
    __HAL_RCC_USART1_CLK_DISABLE();

    /**USART1 GPIO Configuration
    PA9     ------> USART1_TX
    PA10     ------> USART1_RX
    */
    HAL_GPIO_DeInit(GPIOA, GPIO_PIN_9|GPIO_PIN_10);

    /* USART1 interrupt DeInit */
    HAL_NVIC_DisableIRQ(USART1_IRQn);
  /* USER CODE BEGIN USART1_MspDeInit 1 */

  /* USER CODE END USART1_MspDeInit 1 */
  }
  else if(huart->Instance==USART2)
  {
  /* USER CODE BEGIN USART2_MspDeInit 0 */

  /* USER CODE END USART2_MspDeInit 0 */
    /* Peripheral clock disable */
    __HAL_RCC_USART2_CLK_DISABLE();

    /**USART2 GPIO Configuration
    PA2     ------> USART2_TX
    PA3     ------> USART2_RX
    */
    HAL_GPIO_DeInit(GPIOA, USART_TX_Pin|USART_RX_Pin);

    /* USART2 interrupt DeInit */
    HAL_NVIC_DisableIRQ(USART2_IRQn);
  /* USER CODE BEGIN USART2_MspDeInit 1 */

  /* USER CODE END USART2_MspDeInit 1 */
  }

}

/* USER CODE BEGIN 1 */

/* USER CODE END 1 */

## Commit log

2023-01-03 Create Projecteur LED.stl
    Modélisation du projecteur V1
2023-01-03 Organisation dossier
    Organisation des dossiers 3D
2023-01-03 Revert "Organisation dossier"
2023-01-03 Revert "Organisation dossier"
    This reverts commit 5cfc88d0448ceb394c1c2ee58c556ba1233973c3.
2023-01-03 Organisation dossier
    Organisation des dossiers 3D
    Revert "Organisation dossier"
    This reverts commit 5cfc88d0448ceb394c1c2ee58c556ba1233973c3.
2023-01-03 Organisation Modélisation3D
    Organisation des documents
2023-01-03 Create Plan plaque LED.jpg
    Plaque LED
2023-01-03 test
2023-01-03 Architecture du driver moteur
2023-01-03 ALED
2023-01-03 Driver modifié avec les bonnes valeurs et les bonnes datasheet
2023-01-03 Remove 3D model
2023-01-03 Remove initial commit.md
2023-01-03 Remove initial commit
2023-01-10 Ajout PCB_Moteur_A4988
    Etendre Carte pour avoir 3 drivers A4988
2023-01-29 Add files via upload
    Version routée numéro 1
2023-01-31 PCB root sans erreurs
2023-01-31 modif push button
2023-01-31 ajout des gerbers
2023-02-07 ajout du nom et augmentation des traces
2023-02-07 derniere MAJ
2023-02-11 Add files via upload
    Deuxième version de cette PCB, problèmes de connexions et d'empreintes résolus
2023-02-28 Add files via upload
    Version du 28/02 du pcb de contrôle (ajout d'un système de driver pour le ventilo)
2023-03-01 Add files via upload
    Après remarques du professeur : Erreurs de routage (CRC) corrigées, changement de l'empreinte du connecteur LED par un jst (et correction des empreintes connecteurs DMX), connexion de l'uart pour la 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
2023-04-30 Update README.md
    Ajout des parties sur le DMX et sur les Driver des Moteurs
2023-04-30 PCB moteur version final
2023-04-30 PCB moteur version final test
2023-04-30 Code de gestion du DMX
